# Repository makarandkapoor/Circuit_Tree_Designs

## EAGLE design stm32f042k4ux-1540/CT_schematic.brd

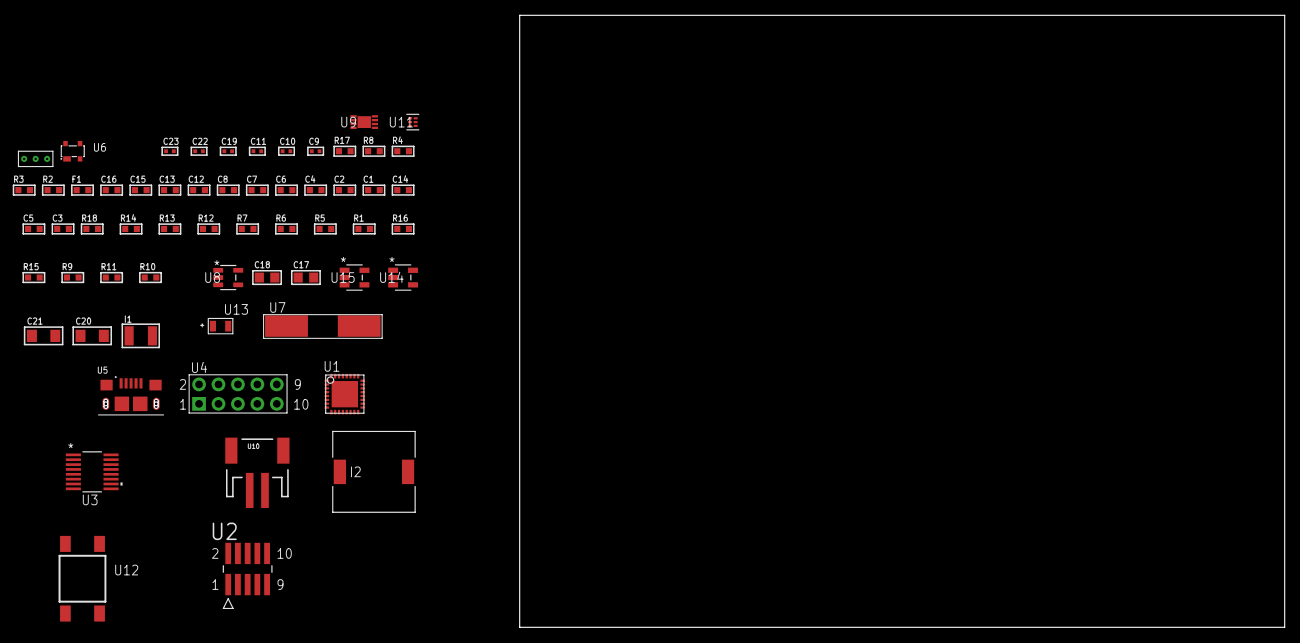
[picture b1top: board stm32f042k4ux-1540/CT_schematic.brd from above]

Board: 2 copper layers, 60 parts (0 on the bottom side), 40 nets, no tracks yet.

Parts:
C1, C2, C4: 1e-07; C0603
C3, C5: 4.7e-06; C0603
C6, C7: 1e-08; C0603
C8, C12, C13, C15, C16: 1e-06; C0603
C9, C10: 1e-11; C0402
C11, C19: 1e-07; C0402
C14: 2.2e-07; C0603
C17, C18: 1e-05; C0805
C20, C21: 1e-05; C1206
C22, C23: 1e-08; C0402
F1: 240.0; L0603
I1: 1e-05; L1210
I2: 5.2e-06; DR1040
R1, R5, R6, R7, R12, R13, R18: 10000.0; R0603
R2: 1000.0; R0603
R3: 1270.0; R0603
R4: 4700.0; R0603
R8: 5.0; R0603
R9: 100000.0; R0603
R10: 309473.68421053; R0603
R11: 1000000.0; R0603
R14: 18000.0; R0603
R15: 470000.0; R0603
R16: 120000.0; R0603
R17: 2000.0; R0603
U1: stm32f042k4u6; UFQFPN32
U2: FTSH-105-01-L-DV-K; SAMTEC_FTSH-105-01-L-DV-K
U3: LTC2804CGN-1#PBF; SSOP-16
U4: HTSS-105-01-G-D
U5: 10118193-0001LF; FCI_10118193-0001LF
U6: prtr5v0u2ax; SOT143B
U7: ABLS-25.000MHZ-B2F-T
U8: ltc3406es5; TSOT-23-5
U9: MCP73831T-2ACI/MC; DFN8_2X3MC
U10: S2B-PH-SM4-TB(LF)(SN); JST-2-SMD
U11: TPS3895ADRYR; SON-6
U12: 4-1437565-2; SW_4-1437565-2
U13: Q65110A2395; LGM67K-G1J2-24-Z
U14, U15: nc7sz125m5x; NC7SZ125M5X
U16: Dummy; DUMMY_PACKAGE_125

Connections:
CLK_CRYSTAL_U1_2: C9.1, U1.2, U7.1
CLK_CRYSTAL_U1_3: C10.1, U1.3, U7.2
GND: C1.2, C2.2, C3.2, C4.2, C5.2, C6.2, C7.2, C8.2, C9.2, C10.2, C11.2, C12.2, C13.2, C15.2, C16.2, C17.2, C18.1, C18.2, C19.2, C20.2, C21.2, C22.2, C23.2, R2.2, R8.2, R10.2, R14.2, R16.2, R17.2, U1.EPAD, U2.3, U2.5, U3.8, U4.9, U5.5, U5.6, U5.7, U5.8, U5.9, U6.1, U8.2, U9.6, U9.9, U10.2, U11.2, U13.C, U14.2, U14.3, U15.1, U15.3, U16.1
INPUT_USBPOWER_5V: C20.1, R18.2, U5.1, U6.4, U9.1, U9.2
NET_U1_4: R4.1, U1.4, U15.4
NET_U1_5: C6.1, C7.1, C8.1, F1.1, U1.5
NET_U1_31: R3.1, U1.31, U13.A
NET_U1_32: R1.1, U1.32, U12.3, U12.4
NET_U2_9: R8.1, U2.9
NET_U3_6: C12.1, U3.6
NET_U3_7: C14.1, I1.2, U3.7
NET_U3_9: C13.1, U3.9
NET_U3_10: C14.2, U3.10
NET_U3_11: R9.1, U3.11
NET_U4_3: U3.1, U4.3
NET_U4_4: U3.2, U4.4
NET_U4_5: U3.3, U4.5
NET_U4_6: U3.4, U4.6
NET_U8_3: I2.1, U8.3
NET_U8_5: R10.1, R11.1, U8.5
NET_U8_ATNET_3: I2.2, R11.2
NET_U9_5: R18.1, U9.5
NET_U9_8: R17.1, U9.8
NET_U11_1: R13.1, R14.1, U11.1
NET_U11_3: R15.2, R16.1, U11.3
NET_U11_4: R12.1, U11.4, U14.4, U15.2
NET_U12_1: R2.1, U12.1, U12.2
PROC_PA4: U1.10, U16.2
PROC_PA5: U1.11, U16.3
PROC_SYS_SWCLK: R6.1, U1.24, U2.4
PROC_SYS_SWDIO: R7.1, U1.23, U2.2
PROC_USART2_CTS: U1.6, U3.13
PROC_USART2_RTS: U1.7, U3.15
PROC_USART2_RX: U1.9, U3.16
PROC_USART2_TX: U1.8, U3.14
PROC_USB_DM: U1.21, U5.2, U6.3
PROC_USB_DP: U1.22, U5.3, U6.2
RST_OUT_U2_JTAG_RST_B: R5.1, U2.10, U14.1
VCC_S1_3V7: C17.1, C21.1, U8.4, U9.3, U9.4, U10.1
VCC_TIER1_2V5: C1.1, C2.1, C3.1, C4.1, C5.1, C11.1, C15.1, C16.1, C18.2, C19.1, C22.1, C23.1, F1.2, I1.1, I2.2, R1.2, R3.2, R4.2, R5.2, R6.2, R7.2, R9.2, R11.2, R12.2, R13.2, R15.1, U1.1, U1.17, U2.1, U3.5, U3.12, U11.6, U14.5, U15.5

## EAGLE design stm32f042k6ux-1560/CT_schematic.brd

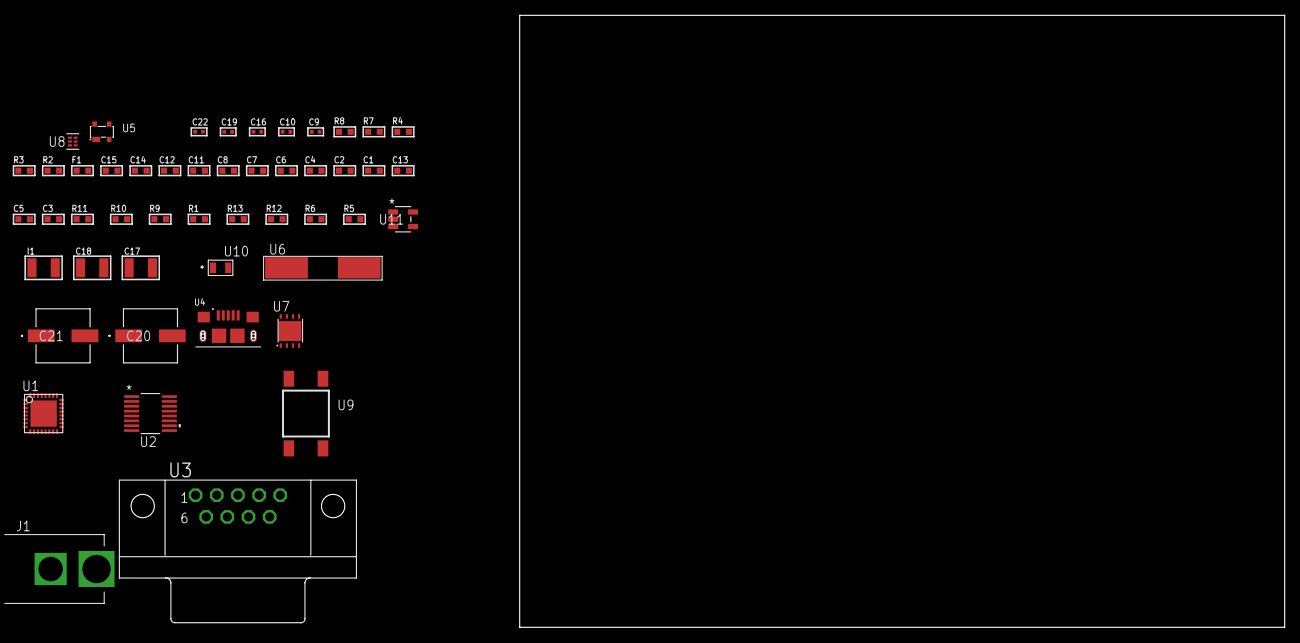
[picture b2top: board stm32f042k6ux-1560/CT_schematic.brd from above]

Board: 2 copper layers, 49 parts (0 on the bottom side), 32 nets, no tracks yet.

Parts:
C1, C2, C4: 1e-07; C0603
C3, C5: 4.7e-06; C0603
C6, C7: 1e-08; C0603
C8, C11, C12, C14, C15: 1e-06; C0603
C9, C10: 1e-11; C0402
C13: 2.2e-07; C0603
C16, C22: 1e-08; C0402
C17, C18: 1e-05; C1210
C19: 1e-07; C0402
C20, C21: 0.0001; EXV-9H
F1: 240.0; L0603
I1: 1e-05; L1210
J1: PJ-037B; PJ-037B_PACKAGE
R1, R9, R10: 10000.0; R0603
R2, R8: 1000.0; R0603
R3: 1270.0; R0603
R4: 4700.0; R0603
R5, R6: 100000.0; R0603
R7: 1500.0; R0603
R11: 18000.0; R0603
R12: 470000.0; R0603
R13: 120000.0; R0603
U1: stm32f042k6u6; UFQFPN32
U2: LTC2804CGN-1#PBF; SSOP-16
U3: 182-009-113R531; 182-009-MALE
U4: 10118193-0001LF; FCI_10118193-0001LF
U5: prtr5v0u2ax; SOT143B
U6: ABLS-25.000MHZ-B2F-T
U7: LP3878SDX-ADJ/NOPB; WSON-8
U8: TPS3895ADRYR; SON-6
U9: 4-1437565-2; SW_4-1437565-2
U10: Q65110A2395; LGM67K-G1J2-24-Z
U11: nc7sz125m5x; NC7SZ125M5X

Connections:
CLK_CRYSTAL_U1_2: C9.1, U1.2, U6.1
CLK_CRYSTAL_U1_3: C10.1, U1.3, U6.2
GND: C1.2, C2.2, C3.2, C4.2, C5.2, C6.2, C7.2, C8.2, C9.2, C10.2, C11.2, C12.2, C14.2, C15.2, C16.2, C17.2, C18.2, C19.2, C20.2, C21.2, C22.2, J1.2, R2.2, R8.2, R11.2, R13.2, U1.EPAD, U2.8, U3.5, U4.5, U4.6, U4.7, U4.8, U4.9, U5.1, U7.3, U7.PAD, U8.2, U10.C, U11.1, U11.3
NET_U1_4: R4.1, U1.4, U11.4
NET_U1_5: C6.1, C7.1, C8.1, F1.1, U1.5
NET_U1_31: R3.1, U1.31, U10.A
NET_U1_32: R1.1, U1.32, U9.3, U9.4
NET_U2_6: C11.1, U2.6
NET_U2_7: C13.1, I1.2, U2.7
NET_U2_9: C12.1, U2.9
NET_U2_10: C13.2, U2.10
NET_U2_11: R5.1, U2.11
NET_U3_2: U2.1, U3.2
NET_U3_3: U2.3, U3.3
NET_U3_7: U2.2, U3.7
NET_U3_8: U2.4, U3.8
NET_U5_4: U4.1, U5.4
NET_U7_1: C16.1, U7.1
NET_U7_6: R7.2, R8.1, U7.6
NET_U7_8: R6.1, U7.8
NET_U8_1: R10.1, R11.1, U8.1
NET_U8_3: R12.2, R13.1, U8.3
NET_U8_4: R9.1, U8.4, U11.2
NET_U9_1: R2.1, U9.1, U9.2
PROC_USART2_CTS: U1.6, U2.13
PROC_USART2_RTS: U1.7, U2.15
PROC_USART2_RX: U1.9, U2.16
PROC_USART2_TX: U1.8, U2.14
PROC_USB_DM: U1.21, U4.2, U5.3
PROC_USB_DP: U1.22, U4.3, U5.2
VCC_S1_11V6: C17.1, C20.1, C21.1, J1.1, R6.2, U7.4
VCC_TIER1_2V5: C1.1, C2.1, C3.1, C4.1, C5.1, C14.1, C15.1, C18.1, C19.1, C22.1, F1.2, I1.1, R1.2, R3.2, R4.2, R5.2, R7.1, R9.2, R10.2, R12.1, U1.1, U1.17, U2.5, U2.12, U7.5, U8.6, U11.5

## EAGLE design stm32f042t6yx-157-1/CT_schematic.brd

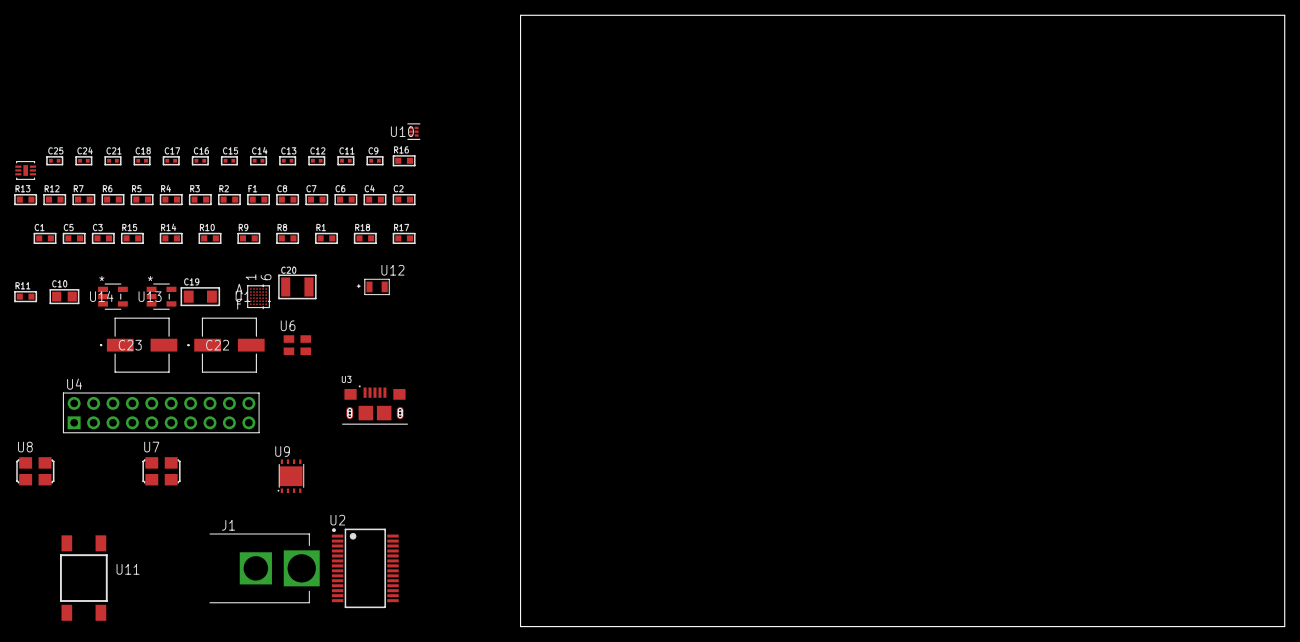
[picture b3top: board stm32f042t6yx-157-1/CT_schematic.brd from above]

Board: 2 copper layers, 122.6 x 80.0 mm, 59 parts (0 on the bottom side), 32 nets, no tracks yet.

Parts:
C1, C2, C4: 1e-07; C0603
C3, C5: 4.7e-06; C0603
C6, C7: 1e-08; C0603
C8: 1e-06; C0603
C9, C11, C12, C13, C14, C21: 1e-07; C0402
C10: 4.7e-06; C0805
C15, C16, C17, C18, C24, C25: 1e-08; C0402
C19: 1e-05; C1206
C20: 1e-05; C1210
C22, C23: 0.0001; EXV-9H
F1: 240.0; L0603
J1: PJ-037B; PJ-037B_PACKAGE
R1, R8, R9, R10, R14, R15: 10000.0; R0603
R2, R13: 1000.0; R0603
R3: 1600.5; R0603
R4, R7: 4700.0; R0603
R5, R6: 2200.0; R0603
R11: 100000.0; R0603
R12: 2231.0; R0603
R16: 9100.0; R0603
R17: 680000.0; R0603
R18: 120000.0; R0603
U1: stm32f042t6y7; WLCSP36
U2: FT232RL-REEL; SSOP-28
U3: 10118193-0001LF; FCI_10118193-0001LF
U4: TST-110-05-T-D-RA
U5: SI7006-A20-IM; DFN-6
U6: ASEK-32.768KHz-ECST; ASEK
U7: ASFL1-12MHZ-NCS; ASFL1
U8: ASFL1-25MHZ-NCS; ASFL1
U9: LP3878SDX-ADJ/NOPB; WSON-8
U10: TPS3895ADRYR; SON-6
U11: 4-1437565-2; SW_4-1437565-2
U12: Q65110A2395; LGM67K-G1J2-24-Z
U13, U14: nc7sz125m5x; NC7SZ125M5X

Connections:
CLK_U1_B5: U1.B5, U8.3
CLK_U1_B6: U1.B6, U6.3
CLK_U2_27: U2.27, U7.3
GND: C1.2, C2.2, C3.2, C4.2, C5.2, C6.2, C7.2, C8.2, C9.2, C10.2, C11.2, C12.2, C13.2, C14.2, C15.2, C16.2, C17.2, C18.2, C19.2, C20.2, C21.2, C22.2, C23.2, C24.2, C25.2, J1.2, R2.2, R9.2, R13.2, R16.2, R18.2, U1.D6, U1.F1, U2.7, U2.18, U2.21, U2.25, U2.26, U3.5, U3.6, U3.7, U3.8, U3.9, U4.4, U4.6, U4.8, U4.10, U4.12, U4.14, U4.16, U4.18, U4.20, U5.2, U5.7, U6.2, U7.2, U8.2, U9.3, U9.PAD, U10.2, U12.C, U13.2, U13.3, U14.1, U14.3
NET_U1_B4: R5.1, U1.B4, U5.6
NET_U1_C1: R6.1, U1.C1, U5.1
NET_U1_D5: R4.1, U1.D5, U14.4
NET_U1_E5: C6.1, C7.1, C8.1, F1.1, U1.E5
NET_U1_F5: R3.1, U1.F5, U12.A
NET_U1_F6: R1.1, U1.F6, U11.3, U11.4
NET_U2_14: R8.1, U2.14
NET_U2_17: C11.1, U2.17
NET_U2_19: R9.1, U2.19
NET_U3_1: R7.1, U3.1
NET_U3_2: U2.16, U3.2
NET_U3_3: U2.15, U3.3
NET_U9_1: C18.1, U9.1
NET_U9_6: R12.2, R13.1, U9.6
NET_U9_8: R11.1, U9.8
NET_U10_1: R15.1, R16.1, U10.1
NET_U10_3: R17.2, R18.1, U10.3
NET_U10_4: R14.1, U10.4, U13.4, U14.2
NET_U11_1: R2.1, U11.1, U11.2
PROC_SYS_SWCLK: U1.B2, U4.9
PROC_SYS_SWDIO: U1.B1, U4.7
PROC_USART1_CTS: U1.C2, U2.3
PROC_USART1_RTS: U1.A1, U2.11
PROC_USART1_RX: U1.A4, U2.1
PROC_USART1_TX: U1.C4, U2.5
RST_OUT_U4_SRESET_B: R10.1, U4.15, U13.1
VCC_S1_11V0: C19.1, C22.1, C23.1, J1.1, R11.2, U9.4
VCC_TIER1_3V3: C1.1, C2.1, C3.1, C4.1, C5.1, C9.1, C10.1, C12.1, C13.1, C14.1, C15.1, C16.1, C17.1, C20.1, C21.1, C24.1, C25.1, F1.2, R1.2, R3.2, R4.2, R5.2, R6.2, R8.2, R10.2, R12.1, R14.2, R15.2, R17.1, U1.A5, U1.E1, U2.4, U2.20, U4.1, U5.5, U6.4, U7.4, U8.4, U9.5, U10.6, U13.5, U14.5

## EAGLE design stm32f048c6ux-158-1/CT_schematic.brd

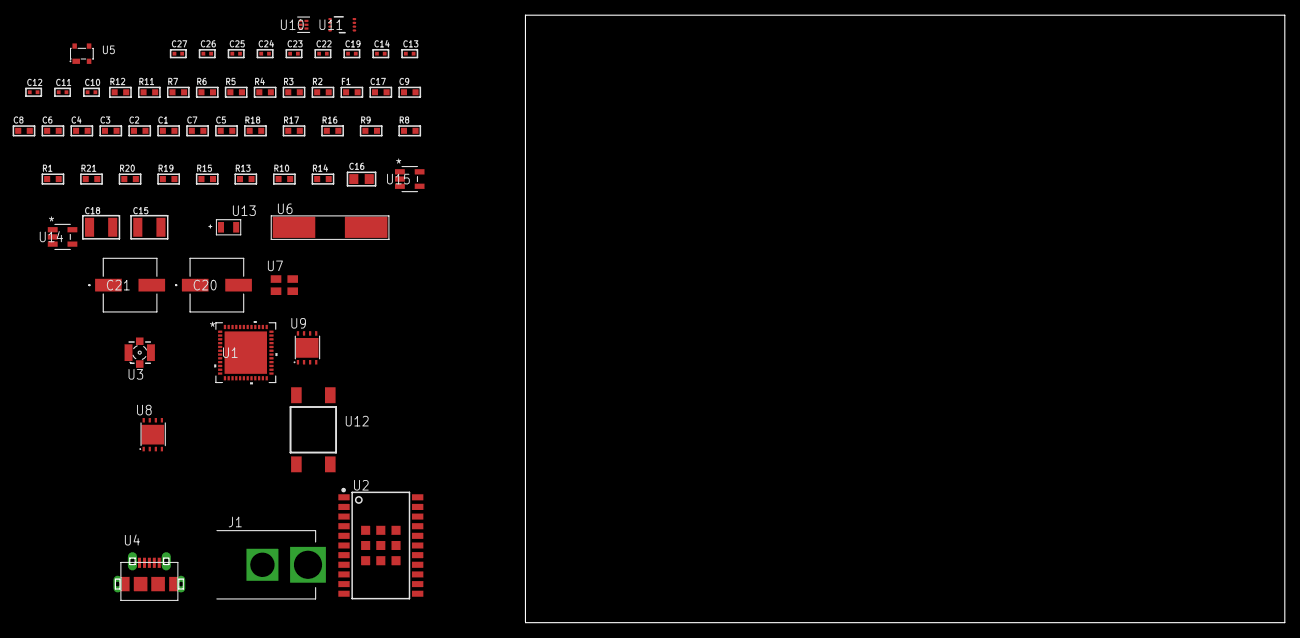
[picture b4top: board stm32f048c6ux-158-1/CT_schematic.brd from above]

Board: 2 copper layers, 154.0 x 80.0 mm, 65 parts (0 on the bottom side), 34 nets, no tracks yet.

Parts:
C1, C9: 1e-06; C0603
C2, C3, C4, C6: 1e-07; C0603
C5, C7: 4.7e-06; C0603
C8: 1e-08; C0603
C10, C11: 1e-11; C0402
C12, C19, C23, C25: 1e-07; C0402
C13, C14, C22, C24, C26, C27: 1e-08; C0402
C15, C18: 1e-05; C1210
C16: 1e-05; C0805
C17: 8e-07; R0603
C20, C21: 0.0001; EXV-9H
F1: 240.0; L0603
J1: PJ-037B; PJ-037B_PACKAGE
R1, R8, R9, R16, R17: 10000.0; R0603
R2, R12: 1000.0; R0603
R3: 910.0; R0603
R4, R5: 4700.0; R0603
R6, R7: 2200.0; R0603
R10, R13, R15: 100000.0; R0603
R11: 806.0; R0603
R14: 153694.38; R0603
R18: 82000.0; R0603
R19: 300000.0; R0603
R20: 120000.0; R0603
R21: 200000.0; R0603
U1: stm32f048c6u7; UFQFPN48
U2: A2200-A
U3: 73412-0114; COAXIAL_C
U4: 47590-0001; MICRO_USB_AB
U5: prtr5v0u2ax; SOT143B
U6: ABLS-25.000MHZ-B2F-T
U7: ASEK-2-32.768KHz-ECST; ASEK
U8: LP3878SDX-ADJ/NOPB; WSON-8
U9: LP2951ACSDX/NOPB; WSON-8
U10: TPS3895ADRYR; SON-6
U11: LSF0102DCTR; DCU0008A_N
U12: 4-1437565-2; SW_4-1437565-2
U13: Q65110A2395; LGM67K-G1J2-24-Z
U14, U15: nc7sz125m5x; NC7SZ125M5X

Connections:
CLK_CRYSTAL_U1_5: C10.1, U1.5, U6.1
CLK_CRYSTAL_U1_6: C11.1, U1.6, U6.2
CLK_U1_3: U1.3, U7.3
GND: C1.2, C2.2, C3.2, C4.2, C5.2, C6.2, C7.2, C8.2, C9.2, C10.2, C11.2, C12.2, C13.2, C14.2, C15.2, C16.2, C17.2, C18.2, C19.2, C20.2, C21.2, C22.2, C23.2, C24.2, C25.2, C26.2, C27.2, J1.2, R2.2, R8.2, R12.2, R15.2, R18.2, R20.2, U1.8, U1.23, U1.35, U1.47, U1.49, U2.7, U2.8, U2.23, U2.24, U2.25, U2.26, U2.27, U2.28, U2.29, U2.30, U2.31, U4.5, U4.6, U4.7, U4.8, U4.9, U5.1, U7.2, U8.3, U8.PAD, U9.3, U9.4, U9.PAD, U10.2, U11.1, U13.C, U14.1, U14.3, U15.1, U15.3
NET_U1_7: R5.1, U1.7, U15.4
NET_U1_9: C8.1, C9.1, F1.1, U1.9
NET_U1_20: R8.1, U1.20
NET_U1_21: R6.1, U1.21, U11.4
NET_U1_22: R7.1, U1.22, U11.3
NET_U1_45: R3.1, U1.45, U13.A
NET_U1_46: R1.1, U1.46, U12.3, U12.4
NET_U2_2: R9.2, U2.2
NET_U2_17: R9.1, U2.17
NET_U2_22: R4.1, U2.22, U14.4
NET_U3_1: U2.11, U3.1
NET_U3_2: U2.10, U3.2, U3.3, U3.4
NET_U5_4: U4.1, U5.4
NET_U8_1: C14.1, U8.1
NET_U8_6: R11.2, R12.1, U8.6
NET_U8_8: R10.1, U8.8
NET_U9_5: R13.1, U9.5
NET_U9_7: R14.2, R15.1, U9.7
NET_U10_1: R17.1, R18.1, U10.1
NET_U10_3: R19.2, R20.1, U10.3
NET_U10_4: R16.1, U10.4, U14.2, U15.2
NET_U11_8: R21.1, U11.8
NET_U12_1: R2.1, U12.1, U12.2
PROC_I2C1_SCL_TOXCVR: U2.15, U11.5
PROC_I2C1_SDA_TOXCVR: U2.16, U11.6
PROC_USB_DM: U1.32, U4.2, U5.3
PROC_USB_DP: U1.33, U4.3, U5.2
VCC_S1_14V5: C15.1, C17.1, C20.1, C21.1, J1.1, R10.2, U8.4, U9.8
VCC_TIER1_1V8: C1.1, C2.1, C3.1, C4.1, C5.1, C6.1, C7.1, C13.1, C16.1, C19.1, C24.1, C25.1, C26.1, C27.1, F1.2, R1.2, R3.2, R5.2, R6.2, R7.2, R11.1, R16.2, R17.2, R19.1, U1.1, U1.24, U1.36, U1.48, U7.4, U8.5, U10.6, U11.2, U14.5, U15.5
VCC_TIER1_3V3: C12.1, C18.1, C22.1, C23.1, R4.2, R13.2, R14.1, R21.2, U2.20, U9.1, U11.7

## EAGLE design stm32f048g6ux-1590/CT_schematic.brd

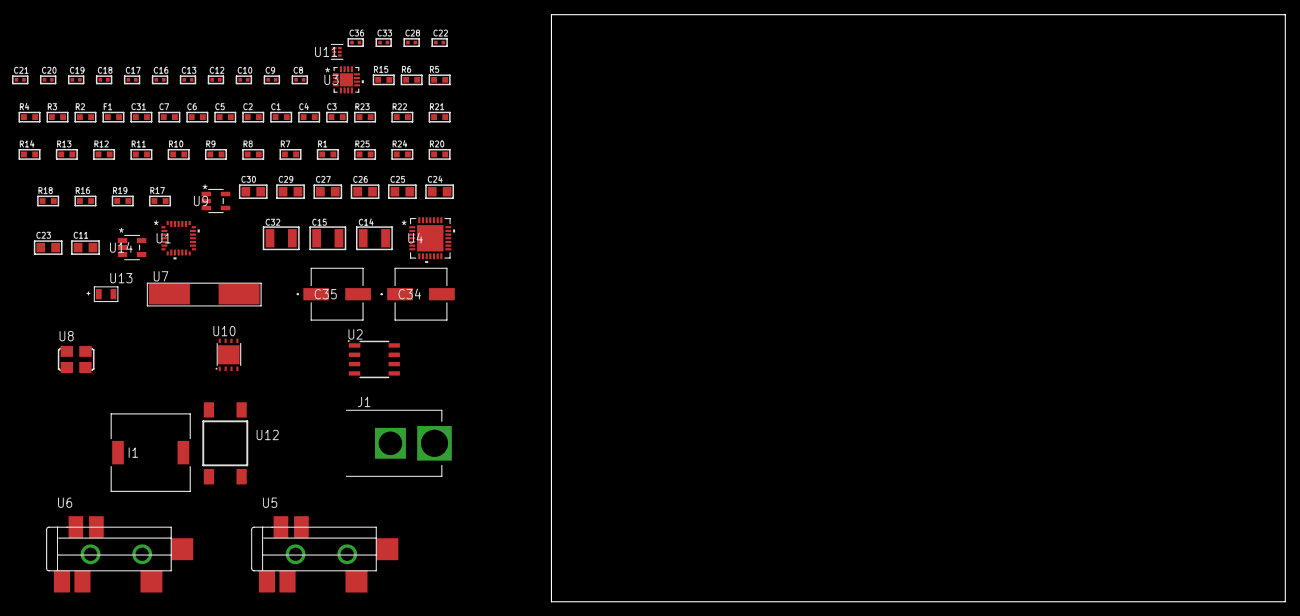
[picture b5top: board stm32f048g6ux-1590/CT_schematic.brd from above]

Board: 2 copper layers, 100.0 x 80.0 mm, 78 parts (0 on the bottom side), 38 nets, no tracks yet.

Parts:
C1, C2: 1e-07; C0603
C3, C4: 4.7e-06; C0603
C5, C6: 1e-08; C0603
C7, C31: 1e-06; C0603
C8, C9: 1e-11; C0402
C10, C28, C36: 1e-08; C0402
C11: 4.7e-06; C0805
C12, C13, C18, C19, C20, C21, C22, C33: 1e-07; C0402
C14, C15: 2.2e-05; C1210
C16, C17: 1e-09; C0402
C23, C24, C25, C26, C27, C29, C30: 1e-05; C0805
C32: 1e-05; C1210
C34, C35: 0.0001; EXV-9H
F1: 240.0; L0603
I1: 7e-06; DR1040
J1: PJ-037B; PJ-037B_PACKAGE
R1, R7, R8, R9, R10, R11, R21, R22: 10000.0; R0603
R2: 1000.0; R0603
R3: 910.0; R0603
R4: 4700.0; R0603
R5, R6: 2200.0; R0603
R12, R13, R14: 47000.0; R0603
R15: 680.0; R0603
R16: 490000.0; R0603
R17: 1000000.0; R0603
R18, R20: 100000.0; R0603
R19: 153694.38; R0603
R23: 82000.0; R0603
R24: 300000.0; R0603
R25: 120000.0; R0603
U1: stm32f048g6u7; UFQFPN28
U2: AT25080B-SSHL-T; SOIC-8
U3: MMA8451QT; QFN-16
U4: WM8731CLSEFL; QFN-28
U5, U6: SJ-43515TS-SMT-TR
U7: ABLS-25.000MHZ-B2F-T
U8: ASFL1-12.288MHZ-EC-T; ASFL1
U9: ltc3406es5; TSOT-23-5
U10: LP2951ACSDX/NOPB; WSON-8
U11: TPS3895ADRYR; SON-6
U12: 4-1437565-2; SW_4-1437565-2
U13: Q65110A2395; LGM67K-G1J2-24-Z
U14: nc7sz125m5x; NC7SZ125M5X

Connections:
CLK_CRYSTAL_U1_2: C8.1, U1.2, U7.1
CLK_CRYSTAL_U1_3: C9.1, U1.3, U7.2
CLK_U4_1: U4.1, U8.3
GND: C1.2, C2.2, C3.2, C4.2, C5.2, C6.2, C7.2, C8.2, C9.2, C10.2, C11.2, C12.2, C13.2, C17.2, C18.2, C19.2, C20.2, C21.2, C22.2, C23.2, C24.2, C25.2, C26.2, C27.2, C28.2, C29.2, C30.1, C30.2, C31.2, C32.2, C33.2, C34.2, C35.2, C36.2, J1.2, R2.2, R7.2, R11.2, R12.2, R13.2, R14.2, R16.2, R20.2, R23.2, R25.2, U1.16, U2.4, U3.5, U3.10, U3.12, U3.17, U4.4, U4.15, U4.19, U4.25, U4.26, U4.29, U5.1, U6.1, U8.2, U9.2, U10.3, U10.4, U10.PAD, U11.2, U13.C, U14.1, U14.3
NET_U1_1: R5.1, U1.1, U3.4
NET_U1_4: R4.1, U1.4, U14.4
NET_U1_5: C5.1, C6.1, C7.1, F1.1, U1.5
NET_U1_15: R7.1, U1.15
NET_U1_20: R6.1, U1.20, U3.6
NET_U1_27: R3.1, U1.27, U13.A
NET_U1_28: R1.1, U1.28, U12.3, U12.4
NET_U2_3: R8.1, U2.3
NET_U2_7: R10.1, U2.7
NET_U3_2: C13.1, U3.2
NET_U3_7: R11.1, U3.7
NET_U4_20: C22.1, C27.1, U4.20
NET_U5_2: C15.1, R13.1, U5.2
NET_U5_5: C14.1, R12.1, U5.5
NET_U6_5: C16.1, C17.1, R14.1, R15.1, U6.5
NET_U9_3: I1.1, U9.3
NET_U9_5: R16.1, R17.1, U9.5
NET_U9_ATNET_3: I1.2, R17.2
NET_U10_5: R18.1, U10.5
NET_U10_7: R19.2, R20.1, U10.7
NET_U11_1: R22.1, R23.1, U11.1
NET_U11_3: R24.2, R25.1, U11.3
NET_U11_4: R21.1, U11.4, U14.2
NET_U12_1: R2.1, U12.1, U12.2
PROC_I2S1_CK: U1.24, U4.7
PROC_I2S1_SD: U1.26, U4.8
PROC_I2S1_WS: U1.23, U4.9, U4.11
PROC_SPI1_MISO: U1.12, U2.2
PROC_SPI1_MOSI: U1.13, U2.5
PROC_SPI1_NSS: R9.1, U1.10, U2.1
PROC_SPI1_SCK: U1.11, U2.6
VCC_S1_5V3: C29.1, C31.1, C34.1, C35.1, J1.1, U9.4, U10.8
VCC_TIER1_1V8: C1.1, C2.1, C3.1, C4.1, C10.1, C12.1, C18.1, C19.1, C20.1, C21.1, C23.1, C24.1, C25.1, C26.1, C30.2, C33.1, C36.1, F1.2, I1.2, R1.2, R3.2, R4.2, R5.2, R6.2, R8.2, R9.2, R10.2, R17.2, R21.2, R22.2, R24.1, U1.17, U1.18, U2.8, U3.1, U4.3, U4.5, U4.12, U4.18, U11.6, U14.5
VCC_TIER1_3V3: C11.1, C28.1, C32.1, R18.2, R19.1, U3.14, U8.4, U10.1

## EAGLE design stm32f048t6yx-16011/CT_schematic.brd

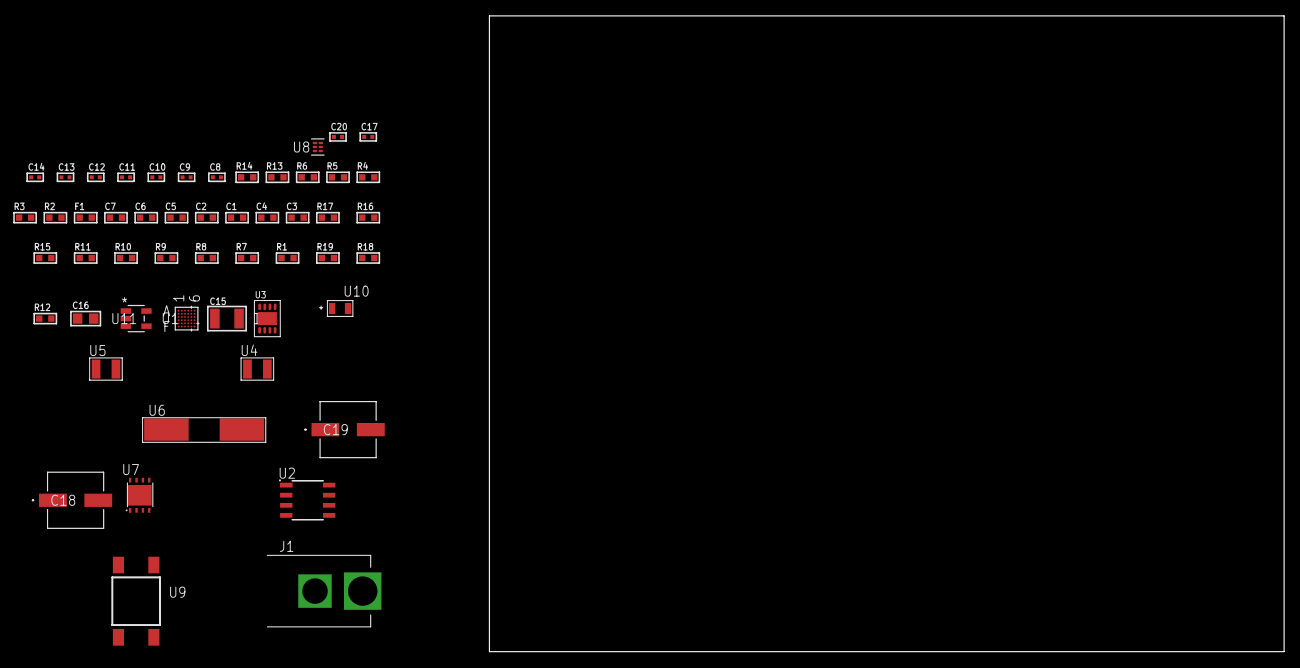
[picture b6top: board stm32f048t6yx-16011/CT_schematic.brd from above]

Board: 2 copper layers, 100.0 x 80.0 mm, 52 parts (0 on the bottom side), 30 nets, no tracks yet.

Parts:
C1, C2: 1e-07; C0603
C3, C4: 4.7e-06; C0603
C5, C6: 1e-08; C0603
C7: 1e-06; C0603
C8, C9, C10, C11: 1e-11; C0402
C12, C14, C20: 1e-08; C0402
C13, C17: 1e-07; C0402
C15: 1e-05; C1210
C16: 1e-05; C0805
C18, C19: 0.0001; EXV-9H
F1: 240.0; L0603
J1: PJ-037B; PJ-037B_PACKAGE
R1, R7, R8, R9, R10, R11, R15, R16: 10000.0; R0603
R2, R14: 1000.0; R0603
R3: 910.0; R0603
R4: 4700.0; R0603
R5, R6: 2200.0; R0603
R12: 100000.0; R0603
R13: 806.0; R0603
R17: 82000.0; R0603
R18: 300000.0; R0603
R19: 120000.0; R0603
U1: stm32f048t6y7; WLCSP36
U2: AT25512N-SH-T; SOIC-8
U3: PCF85063TP/1Z; SON-8
U4, U5: ABS07-32.768KHZ-7-T
U6: ABLS-25.000MHZ-B2F-T
U7: LP3878SDX-ADJ/NOPB; WSON-8
U8: TPS3895ADRYR; SON-6
U9: 4-1437565-2; SW_4-1437565-2
U10: Q65110A2395; LGM67K-G1J2-24-Z
U11: nc7sz125m5x; NC7SZ125M5X

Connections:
CLK_CRYSTAL_U1_B5: C10.1, U1.B5, U6.1
CLK_CRYSTAL_U1_B6: C8.1, U1.B6, U5.1
CLK_CRYSTAL_U1_C5: C11.1, U1.C5, U6.2
CLK_CRYSTAL_U1_C6: C9.1, U1.C6, U5.2
CLK_CRYSTAL_U3_1: U3.1, U4.1
CLK_CRYSTAL_U3_2: U3.2, U4.2
GND: C1.2, C2.2, C3.2, C4.2, C5.2, C6.2, C7.2, C8.2, C9.2, C10.2, C11.2, C12.2, C13.2, C14.2, C15.2, C16.2, C17.2, C18.2, C19.2, C20.2, J1.2, R2.2, R7.2, R14.2, R17.2, R19.2, U1.D6, U1.F1, U2.4, U3.4, U3.PAD, U7.3, U7.PAD, U8.2, U10.C, U11.1, U11.3
NET_U1_A1: R6.1, U1.A1, U3.5
NET_U1_B4: R5.1, U1.B4, U3.6
NET_U1_D5: R4.1, U1.D5, U11.4
NET_U1_E5: C5.1, C6.1, C7.1, F1.1, U1.E5
NET_U1_F2: R7.1, U1.F2
NET_U1_F5: R3.1, U1.F5, U10.A
NET_U1_F6: R1.1, U1.F6, U9.3, U9.4
NET_U2_3: R8.1, U2.3
NET_U2_7: R10.1, U2.7
NET_U3_3: R11.1, U3.3
NET_U7_1: C14.1, U7.1
NET_U7_6: R13.2, R14.1, U7.6
NET_U7_8: R12.1, U7.8
NET_U8_1: R16.1, R17.1, U8.1
NET_U8_3: R18.2, R19.1, U8.3
NET_U8_4: R15.1, U8.4, U11.2
NET_U9_1: R2.1, U9.1, U9.2
PROC_SPI1_MISO: U1.A3, U2.2
PROC_SPI1_MOSI: U1.E6, U2.5
PROC_SPI1_NSS: R9.1, U1.A2, U2.1
PROC_SPI1_SCK: U1.B3, U2.6
VCC_S1_12V2: C15.1, C18.1, C19.1, J1.1, R12.2, U7.4
VCC_TIER1_1V8: C1.1, C2.1, C3.1, C4.1, C12.1, C13.1, C16.1, C17.1, C20.1, F1.2, R1.2, R3.2, R4.2, R5.2, R6.2, R8.2, R9.2, R10.2, R11.2, R13.1, R15.2, R16.2, R18.1, U1.A5, U1.E1, U2.8, U3.8, U7.5, U8.6, U11.5

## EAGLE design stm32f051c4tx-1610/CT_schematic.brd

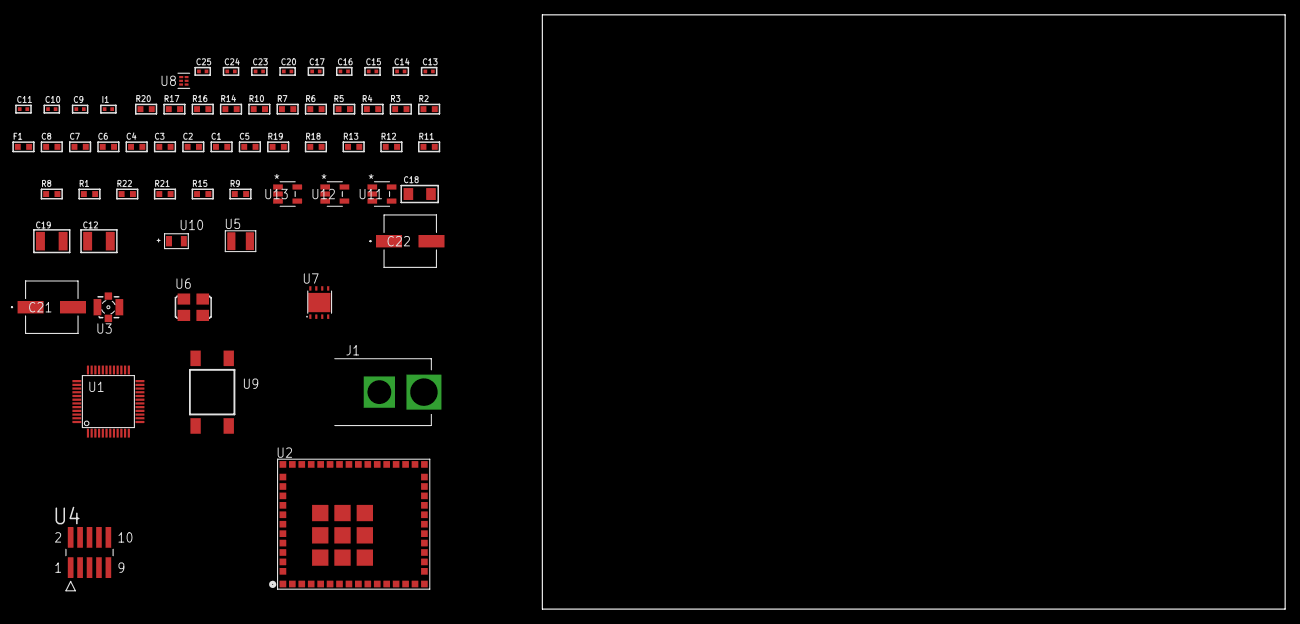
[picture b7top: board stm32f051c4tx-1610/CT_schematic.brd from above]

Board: 2 copper layers, 100.0 x 80.0 mm, 63 parts (0 on the bottom side), 28 nets, no tracks yet.

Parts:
C1, C8: 1e-06; C0603
C2, C3, C4, C6: 1e-07; C0603
C5: 4.7e-06; C0603
C7: 1e-08; C0603
C9, C10: 1e-11; C0402
C11: 1e-12; C0402
C12: 2.2e-05; C1210
C13, C14, C15, C20: 1e-07; C0402
C16, C17, C23, C24, C25: 1e-08; C0402
C18: 1e-05; C1206
C19: 1e-05; C1210
C21, C22: 0.0001; EXV-9H
F1: 240.0; L0603
I1: 3.6e-09; C0402
J1: PJ-037B; PJ-037B_PACKAGE
R1, R8, R11, R12, R13, R18, R19: 10000.0; R0603
R2, R17: 1000.0; R0603
R3: 1600.5; R0603
R4, R5: 4700.0; R0603
R6, R7: 2200.0; R0603
R9, R15: 100000.0; R0603
R10: 2700.0; R0603
R14: 5.0; R0603
R16: 2231.0; R0603
R20: 9100.0; R0603
R21: 680000.0; R0603
R22: 120000.0; R0603
U1: stm32f051c4t7; LQFP48
U2: CC3200MODR1M2AMOBT; LGA63S127P16X13_2050X1750X150
U3: 73412-0114; COAXIAL_C
U4: FTSH-105-01-L-DV-K; SAMTEC_FTSH-105-01-L-DV-K
U5: ABS07-32.768KHZ-7-T
U6: ASFL1-25MHZ-NCS; ASFL1
U7: LP3878SDX-ADJ/NOPB; WSON-8
U8: TPS3895ADRYR; SON-6
U9: 4-1437565-2; SW_4-1437565-2
U10: Q65110A2395; LGM67K-G1J2-24-Z
U11, U12, U13: nc7sz125m5x; NC7SZ125M5X

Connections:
CLK_CRYSTAL_U1_3: C9.1, U1.3, U5.1
CLK_CRYSTAL_U1_4: C10.1, U1.4, U5.2
CLK_U1_5: U1.5, U6.3
GND: C1.2, C2.2, C3.2, C4.2, C5.2, C6.2, C7.2, C8.2, C9.2, C10.2, C11.2, C12.2, C13.2, C14.2, C15.2, C16.2, C17.2, C18.2, C19.2, C20.2, C21.2, C22.2, C23.2, C24.2, C25.2, J1.2, R2.2, R8.2, R9.2, R10.2, R14.2, R17.2, R20.2, R22.2, U1.8, U1.23, U1.47, U2.1, U2.2, U2.16, U2.27, U2.28, U2.30, U2.32, U2.38, U2.43, U2.55, U2.56, U2.57, U2.58, U2.59, U2.60, U2.61, U2.62, U2.63, U3.1, U3.2, U3.3, U3.4, U4.3, U4.5, U6.2, U7.3, U7.PAD, U8.2, U10.C, U11.2, U11.3, U12.1, U12.3, U13.1, U13.3
NET_U1_7: R5.1, U1.7, U13.4
NET_U1_9: C7.1, C8.1, F1.1, U1.9
NET_U1_42: R6.1, U1.42, U2.3
NET_U1_43: R7.1, U1.43, U2.4
NET_U1_44: R8.1, U1.44
NET_U1_45: R3.1, U1.45, U10.A
NET_U1_46: R1.1, U1.46, U9.3, U9.4
NET_U2_21: R9.1, U2.21
NET_U2_23: R10.1, U2.23
NET_U2_35: R4.1, U2.35, U12.4
NET_U3_1: C11.1, I1.1, U3.1
NET_U4_4: R12.1, U4.4
NET_U4_9: R14.1, U4.9
NET_U7_1: C17.1, U7.1
NET_U7_6: R16.2, R17.1, U7.6
NET_U7_8: R15.1, U7.8
NET_U8_1: R19.1, R20.1, U8.1
NET_U8_3: R21.2, R22.1, U8.3
NET_U8_4: R18.1, U8.4, U11.4, U12.2, U13.2
NET_U9_1: R2.1, U9.1, U9.2
PROC_SYS_SWDIO: R13.1, U1.34, U4.2
RST_OUT_U4_JTAG_RST_B: R11.1, U4.10, U11.1
VCC_S1_6V9: C18.1, C21.1, C22.1, J1.1, R15.2, U7.4
VCC_TIER1_3V3: C1.1, C2.1, C3.1, C4.1, C5.1, C6.1, C12.1, C13.1, C14.1, C15.1, C16.1, C19.1, C20.1, C23.1, C24.1, C25.1, F1.2, R1.2, R3.2, R4.2, R5.2, R6.2, R7.2, R11.2, R12.2, R13.2, R16.1, R18.2, R19.2, R21.1, U1.1, U1.24, U1.48, U2.36, U2.37, U2.40, U4.1, U6.4, U7.5, U8.6, U11.5, U12.5, U13.5

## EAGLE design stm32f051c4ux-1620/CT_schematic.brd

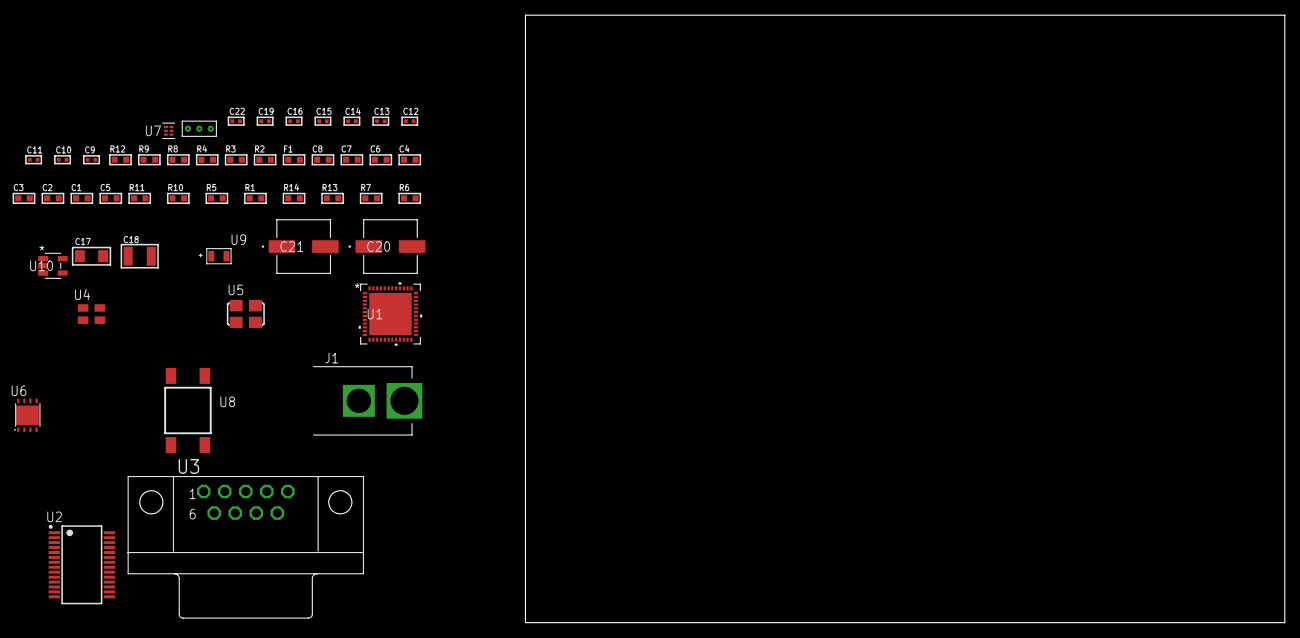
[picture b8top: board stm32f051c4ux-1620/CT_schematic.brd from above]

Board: 2 copper layers, 100.0 x 80.0 mm, 49 parts (0 on the bottom side), 34 nets, no tracks yet.

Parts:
C1, C8: 1e-06; C0603
C2, C3, C4, C6: 1e-07; C0603
C5: 4.7e-06; C0603
C7: 1e-08; C0603
C9, C10, C11, C12, C13, C19: 1e-07; C0402
C14, C15, C16, C22: 1e-08; C0402
C17: 1e-05; C1206
C18: 1e-05; C1210
C20, C21: 0.0001; EXV-9H
F1: 240.0; L0603
J1: PJ-037B; PJ-037B_PACKAGE
R1, R5, R10, R11: 10000.0; R0603
R2, R9: 1000.0; R0603
R3: 1600.5; R0603
R4: 4700.0; R0603
R6, R7: 100000.0; R0603
R8: 2231.0; R0603
R12: 9100.0; R0603
R13: 680000.0; R0603
R14: 120000.0; R0603
U1: stm32f051c4u7; UFQFPN48
U2: ST3241EBPR; SSOP-28
U3: 182-009-113R531; 182-009-MALE
U4: ASEK-32.768KHz-ECST; ASEK
U5: ASFL1-25MHZ-NCS; ASFL1
U6: LP3878SDX-ADJ/NOPB; WSON-8
U7: TPS3895ADRYR; SON-6
U8: 4-1437565-2; SW_4-1437565-2
U9: Q65110A2395; LGM67K-G1J2-24-Z
U10: nc7sz125m5x; NC7SZ125M5X
U11: Dummy; DUMMY_PACKAGE_100

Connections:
CLK_U1_3: U1.3, U4.3
CLK_U1_5: U1.5, U5.3
GND: C1.2, C2.2, C3.2, C4.2, C5.2, C6.2, C7.2, C8.2, C9.2, C12.2, C13.2, C14.2, C15.2, C16.2, C17.2, C18.2, C19.2, C20.2, C21.2, C22.2, J1.2, R2.2, R5.2, R9.2, R12.2, R14.2, U1.8, U1.23, U1.47, U1.49, U2.23, U2.25, U3.5, U4.2, U5.2, U6.3, U6.PAD, U7.2, U9.C, U10.1, U10.3, U11.1
NET_U1_7: R4.1, U1.7, U10.4
NET_U1_9: C7.1, C8.1, F1.1, U1.9
NET_U1_44: R5.1, U1.44
NET_U1_45: R3.1, U1.45, U9.A
NET_U1_46: R1.1, U1.46, U8.3, U8.4
NET_U2_1: C11.1, U2.1
NET_U2_2: C11.2, U2.2
NET_U2_3: C13.1, U2.3
NET_U2_22: R6.1, U2.22
NET_U2_24: C10.2, U2.24
NET_U2_27: C12.1, U2.27
NET_U2_28: C10.1, U2.28
NET_U3_2: U2.4, U3.2
NET_U3_3: U2.9, U3.3
NET_U3_7: U2.5, U3.7
NET_U3_8: U2.10, U3.8
NET_U6_1: C16.1, U6.1
NET_U6_6: R8.2, R9.1, U6.6
NET_U6_8: R7.1, U6.8
NET_U7_1: R11.1, R12.1, U7.1
NET_U7_3: R13.2, R14.1, U7.3
NET_U7_4: R10.1, U7.4, U10.2
NET_U8_1: R2.1, U8.1, U8.2
PROC_ADC_IN0: U1.10, U11.2
PROC_ADC_IN1: U1.11, U11.3
PROC_USART1_CTS: U1.32, U2.13
PROC_USART1_RTS: U1.33, U2.18
PROC_USART1_RX: U1.31, U2.19
PROC_USART1_TX: U1.30, U2.14
VCC_S1_10V4: C17.1, C20.1, C21.1, J1.1, R7.2, U6.4
VCC_TIER1_3V3: C1.1, C2.1, C3.1, C4.1, C5.1, C6.1, C9.1, C14.1, C15.1, C18.1, C19.1, C22.1, F1.2, R1.2, R3.2, R4.2, R6.2, R8.1, R10.2, R11.2, R13.1, U1.1, U1.24, U1.48, U2.26, U4.4, U5.4, U6.5, U7.6, U10.5
